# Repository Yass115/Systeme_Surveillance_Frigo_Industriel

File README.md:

# Système de surveillance d'un frigo industriel

Projet réalisé dans le cadre du cours **Conception et analyse de schémas** — ISIB, cours de M. Rodrigues.

## Objectif du projet

Concevoir une électronique de mesure et de surveillance destinée à être embarquée dans un frigo industriel, capable de détecter et signaler tout comportement anormal (porte oubliée, dérive de température, coupure de courant), depuis le schéma électronique jusqu'au circuit imprimé fini.

## Cahier des charges

| Exigence | Détail |
|---|---|
| Environnement | Boîtier étanche, tenue aux températures négatives |
| Mesure de température | Thermocouples, de préférence type T, connecteurs standards |
| Résolution | 1 °C ou mieux |
| Alerte à distance | En cas de comportement anormal (porte ouverte, baisse anormale de température, …) |
| Alerte locale | Alarme sonore/visuelle sur place |
| Communication | Ethernet |
| Consommation | Minimale |
| Alimentation | Protection contre les coupures de courant (secours sur batterie) |
| Indication | Témoins de fonctionnement (LEDs d'état) |

## Structure du projet

Le cours se déroule en deux volets complémentaires, correspondant aux deux dossiers du dépôt :

### 1. Schématique — `schematic/`
- Analyse du cahier des charges et découpage fonctionnel du système
- Choix et justification des composants (datasheets, calculs de dimensionnement)
- Câblage du schéma électronique complet
- Vérification des règles électriques (ERC)

### 2. Circuit imprimé — `pcb/`
- Placement des composants et contraintes mécaniques (boîtier, connecteurs)
- Routage des pistes (KiCad)
- Respect des règles de conception (largeur de piste, isolation, plan de masse)
- Génération des fichiers de fabrication (Gerbers, BOM, plan de perçage)

## Architecture électronique retenue

| Bloc | Composant | Rôle |
|---|---|---|
| Microcontrôleur | STM32L476 | Traitement, logique de surveillance |
| Mesure température (thermocouple) | MAX31855 + thermocouple type T | Mesure haute précision |
| Mesure température (secours/locale) | DS18B20 | Redondance de mesure |
| Communication | W5500 + MagJack RJ45 | Interface Ethernet |
| Alimentation secteur | HLK-PM01 (230 V → 5 V) | Alimentation principale isolée |
| Régulation | AMS1117-3.3 | Alimentation logique 3,3 V |
| Secours | Pile CR123A | Continuité de service en cas de coupure |

> La zone réseau 230 V est isolée de la basse tension par une barrière d'isolement, conformément aux règles de sécurité électrique.

## Outils utilisés

- **KiCad** — schématique et routage PCB
- **LaTeX** — rédaction du rapport de conception

## Organisation des fichiers

```
├── schematic/          # Fichiers de schéma KiCad, notes de choix de composants
├── pcb/                # Layout, règles de conception, fichiers de fabrication
├── datasheets/         # Documentation des composants clés
├── rapport/            # Rapport LaTeX du projet
└── README.md
```

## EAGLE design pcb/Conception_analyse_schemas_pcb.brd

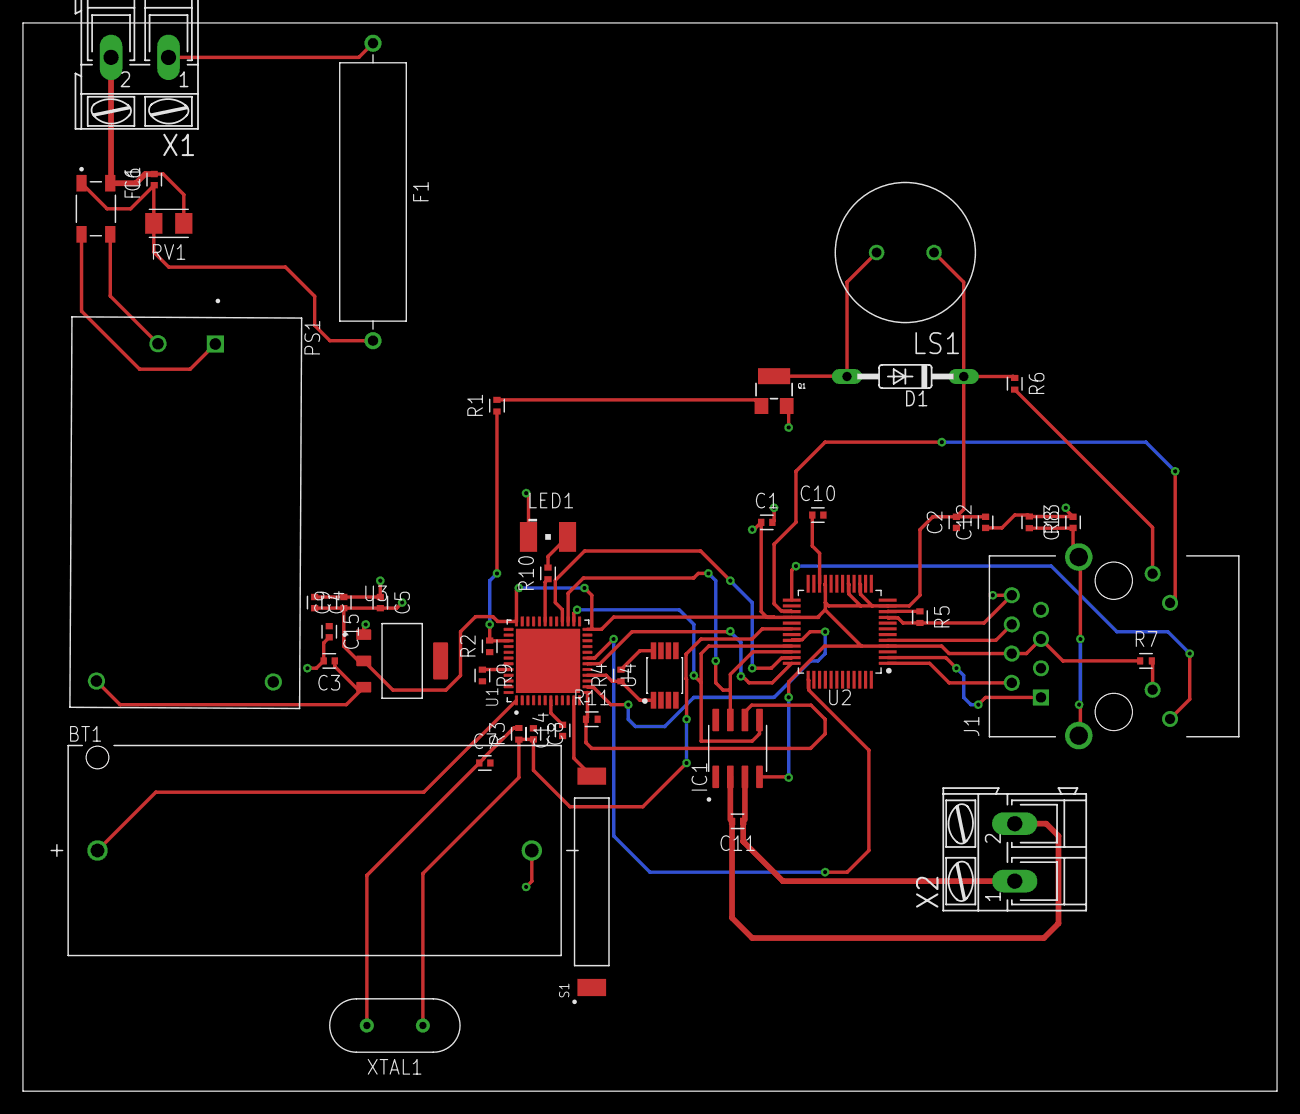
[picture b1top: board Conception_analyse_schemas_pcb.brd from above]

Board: 4 copper layers, 109.2 x 93.0 mm, 45 parts (0 on the bottom side), 41 nets.

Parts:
BT1: 1051; BAT_1051
C1, C2, C9, C12, C14, C15: 100n; CAPC1005X60
C3, C10: 10u; CAPC1005X60
C4: 22u; CAPC1005X60
C5: 47u; CAPC1005X60
C6: CAPC1005X60
C7, C8: 22p; CAPC1005X60
C11: 10n; CAPC1005X60
C13: 4.7n; CAPC1005X60
D1: 1N4148DO35-10; DO35-10
F1: FUSAD2590W70L2150D550B
FL1: DLW43SH510XK2K; FIL_DLW43SH510XK2K
IC1: MAX31855KASA+T; SOIC127P600X175-8N
J1: RJMG1BD3B8K1ANR; CONN_RJMG1BD3B8K1ANR
LED1: LS_T679-D2E2-1; PLCC2
LS1: PS1240P02BT; XDCR_PS1240P02BT
PS1: HLK-PM01; CONV_HLK-PM01
Q1: SOT23-W
R1: 1k; RESC1005X40
R2, R9: 10k; RESC1005X40
R3, R8: 1M; RESC1005X40
R4: 4.7k; RESC1005X40
R5: 12.4k; RESC1005X40
R6, R7: 330; RESC1005X40
R10, R11: RESC1005X40
RV1: VARC3216X102N
S1: PMC-1001THY; SW_PMC-1001THY
U1: STM32L452CCU6; QFN50P700X700X60-49N
U2: W5500_LQFP; QFP50P900X900X160-48N
U3: AMS1117-3.3; SOT229P700X180-4N
U4: DS18B20U_SOP; SOP65P491X110-8N
X1, X2: AK300/2
XTAL1: CRYSTAL_HC49-11L-13.5H; XTALRR488W43L1135T465H1346B

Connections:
3V3: C1.1, C2.2, C4.2, C5.2, C9.1, C12.2, D1.C, IC1.4, J1.R4, J1.R5, LS1.1, R6.1, R7.1, U1.24, U1.36, U2.4, U2.8, U2.11, U2.15, U2.17, U2.21, U2.28, U3.2
5V: C3.1, PS1.4, U3.3
ACTLED: J1.L2, U2.27
AGND: BT1.N, C1.2, C2.1, C3.2, C4.1, C5.1, C7.2, C8.1, C9.2, C10.2, C12.1, C13.2, C15.2, J1.R8, LED1.C, Q1.2, R5.2, R8.1, R9.2, U1.8, U1.23, U1.35, U1.47, U2.3, U2.9, U2.14, U2.16, U2.19, U2.29, U2.48, U3.1
BUZZ: R1.1, R2.2, U1.39
CS: IC1.6, R11.1, U1.13
DQ: R4.1, U1.16, U4.1
INTN: U1.18, U2.36
LINKLED: J1.L4, U2.25
MISO: IC1.7, U1.27, U2.34
MOSI: U1.28, U2.35
unnamed: Q1.1, R1.2
unnamed: F1.1, X1.1
unnamed: D1.A, LS1.2, Q1.3
unnamed: C6.1, F1.2, FL1.1, RV1.2
unnamed: C6.2, FL1.4, RV1.1, X1.2
unnamed: FL1.3, PS1.2
unnamed: FL1.2, PS1.1
unnamed: C7.1, R3.2, U2.31, XTAL1.2
unnamed: C8.2, R3.1, U2.30, XTAL1.1
unnamed: C10.1, U2.22
unnamed: S1.2, U1.11
unnamed: C11.1, IC1.3, X2.1
unnamed: BT1.P, U1.1
unnamed: R5.1, U2.10
unnamed: C11.2, IC1.2, X2.2
unnamed: J1.L1, R6.2
unnamed: J1.L3, R7.2
unnamed: C13.1, J1.1, J1.2, R8.2
unnamed: R9.1, U1.44
unnamed: C14.2, U1.7
unnamed: LED1.A, R10.2
PA10: R10.1, U1.31
RSTN: U1.19, U2.37
RXN: J1.R6, U2.5
RXP: J1.R3, U2.6
S$1: R4.2, U1.9, U1.48, U4.8
SCLK: IC1.5, U1.26, U2.33
SCSN: U1.14, U2.32
TXN: J1.R2, U2.1
TXP: J1.R1, U2.2
